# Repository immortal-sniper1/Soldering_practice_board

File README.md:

# Soldering_practice_board
 just some cheap boards i made to practice SMD soldering

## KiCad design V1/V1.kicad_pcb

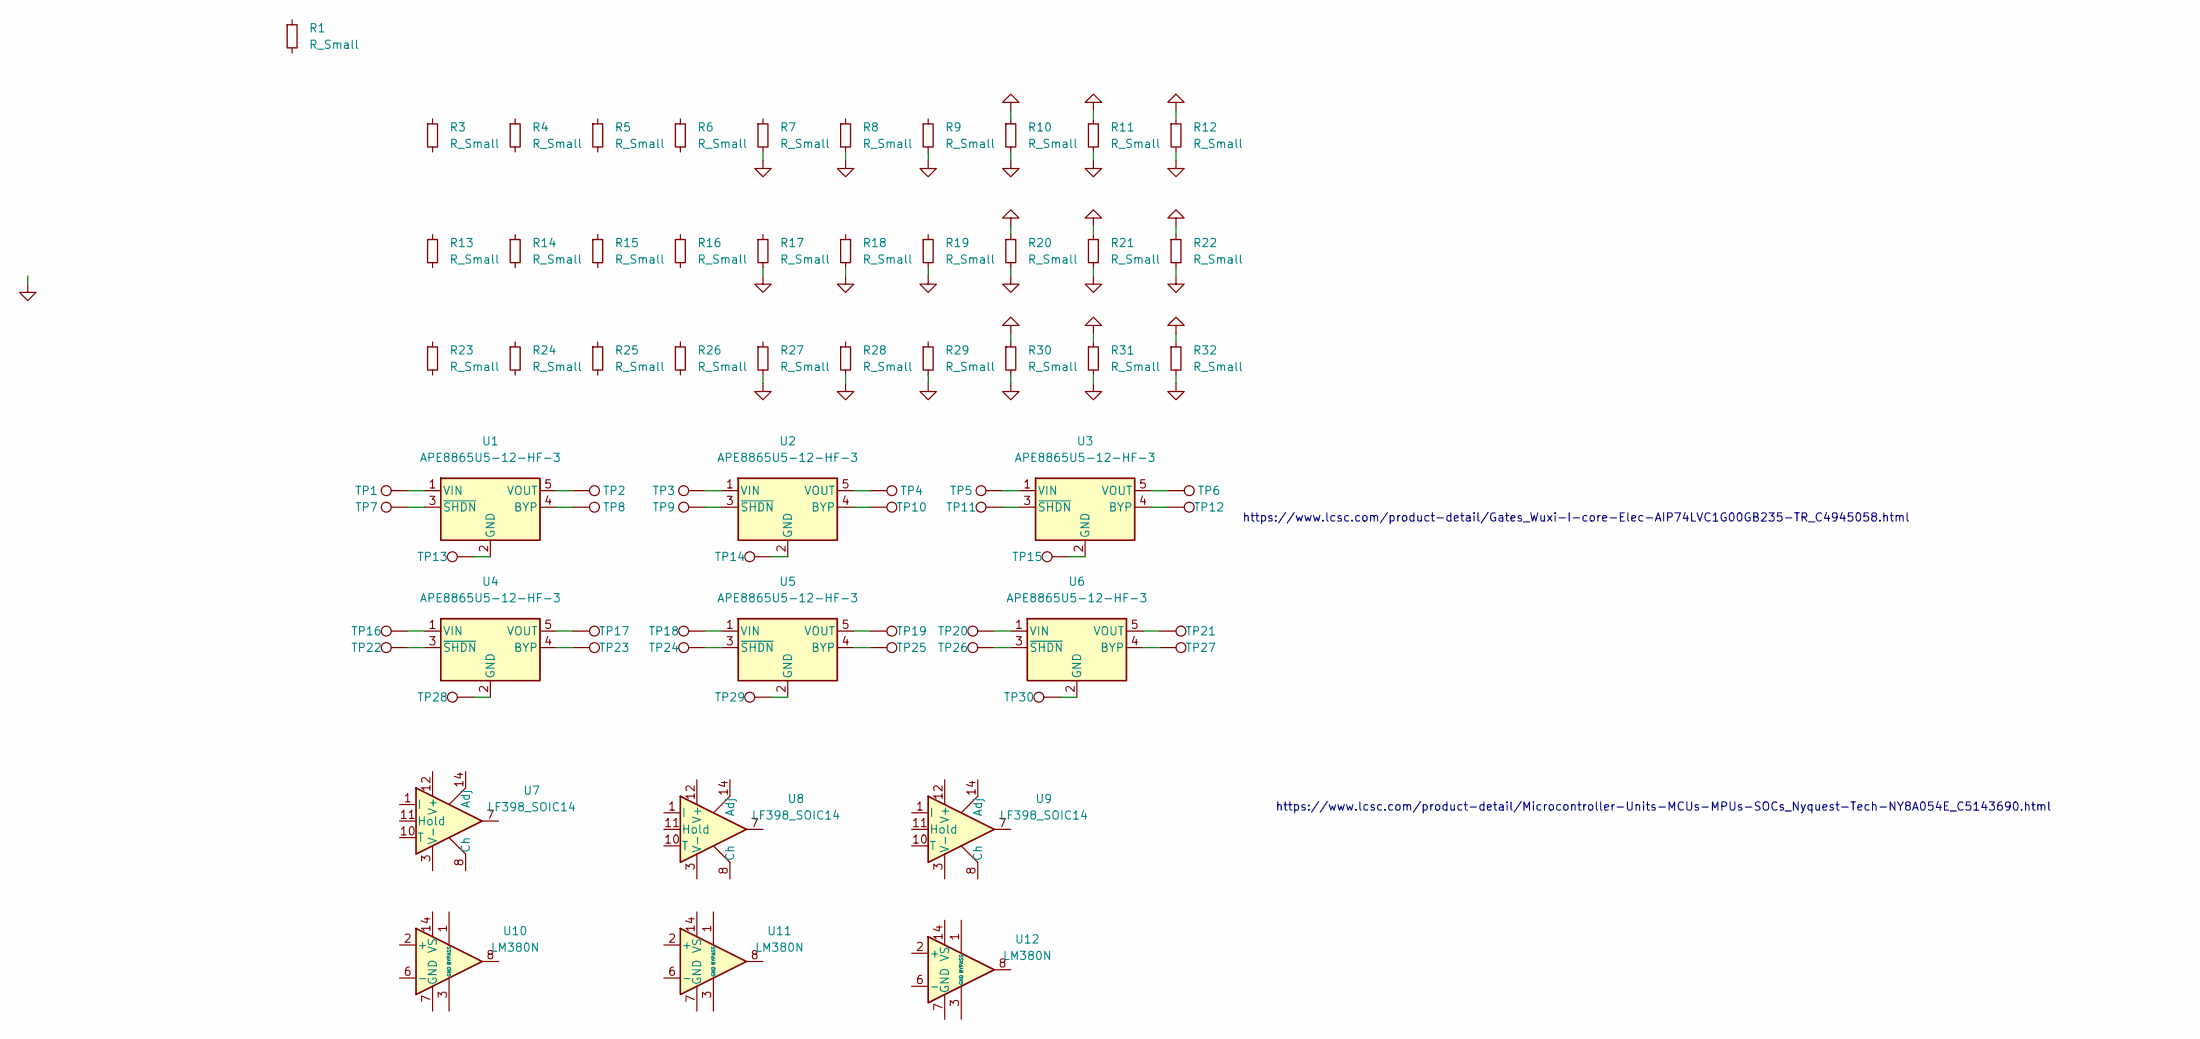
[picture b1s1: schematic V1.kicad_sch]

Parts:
R1: R_Small; 10x10_cm
R3, R4, R5, R6, R7, R8, R9, R10, R11, R12: R_Small; R_0805_2012Metric
R13, R14, R15, R16, R17, R18, R19, R20, R21, R22: R_Small; R_0603_1608Metric
R23, R24, R25, R26, R27, R28, R29, R30, R31, R32: R_Small; R_0402_1005Metric
TP1, TP2, TP3, TP4, TP5, TP6, TP7, TP8, TP9, TP10, TP11, TP12, TP13, TP14, TP15, TP16, TP17, TP18, TP19, TP20, TP21, TP22, TP23, TP24, TP25, TP26, TP27, TP28, TP29, TP30: TestPoint; TestPoint_Keystone_5000-5004_Miniature
U1, U2, U3, U4, U5, U6: APE8865U5-12-HF-3; SOT-353_SC-70-5
U7, U8, U9: LF398_SOIC14; SOIC-14_3.9x8.7mm_P1.27mm
U10, U11, U12: LM380N; DIP-14_W7.62mm

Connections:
GND: R7.2, R8.2, R9.2, R10.1, R10.2, R11.1, R11.2, R12.1, R12.2, R17.2, R18.2, R19.2, R20.1, R20.2, R21.1, R21.2, R22.1, R22.2, R27.2, R28.2, R29.2, R30.1, R30.2, R31.1, R31.2, R32.1, R32.2
unnamed: TP1.1, U1.1 (VIN)
unnamed: TP2.1, U1.5 (VOUT)
unnamed: TP3.1, U2.1 (VIN)
unnamed: TP4.1, U2.5 (VOUT)
unnamed: TP5.1, U3.1 (VIN)
unnamed: TP6.1, U3.5 (VOUT)
unnamed: TP7.1, U1.3 (~SHDN)
unnamed: TP8.1, U1.4 (BYP)
unnamed: TP9.1, U2.3 (~SHDN)
unnamed: TP10.1, U2.4 (BYP)
unnamed: TP11.1, U3.3 (~SHDN)
unnamed: TP12.1, U3.4 (BYP)
unnamed: TP13.1, U1.2 (GND)
unnamed: TP14.1, U2.2 (GND)
unnamed: TP15.1, U3.2 (GND)
unnamed: TP16.1, U4.1 (VIN)
unnamed: TP17.1, U4.5 (VOUT)
unnamed: TP18.1, U5.1 (VIN)
unnamed: TP19.1, U5.5 (VOUT)
unnamed: TP20.1, U6.1 (VIN)
unnamed: TP21.1, U6.5 (VOUT)
unnamed: TP22.1, U4.3 (~SHDN)
unnamed: TP23.1, U4.4 (BYP)
unnamed: TP24.1, U5.3 (~SHDN)
unnamed: TP25.1, U5.4 (BYP)
unnamed: TP26.1, U6.3 (~SHDN)
unnamed: TP27.1, U6.4 (BYP)
unnamed: TP28.1, U4.2 (GND)
unnamed: TP29.1, U5.2 (GND)
unnamed: TP30.1, U6.2 (GND)
unnamed: U10.3 (GND), U10.4 (GND), U10.5 (GND), U10.10 (GND), U10.11 (GND), U10.12 (GND)
unnamed: U11.3 (GND), U11.4 (GND), U11.5 (GND), U11.10 (GND), U11.11 (GND), U11.12 (GND)
unnamed: U12.3 (GND), U12.4 (GND), U12.5 (GND), U12.10 (GND), U12.11 (GND), U12.12 (GND)

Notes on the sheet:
https://www.lcsc.com/product-detail/Gates_Wuxi-I-core-Elec-AIP74LVC1G00GB235-TR_C4945058.html
https://www.lcsc.com/product-detail/Microcontroller-Units-MCUs-MPUs-SOCs_Nyquest-Tech-NY8A054E_C5143690.html

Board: 2 copper layers, 73 parts (0 on the bottom side), 34 nets, no tracks yet.
